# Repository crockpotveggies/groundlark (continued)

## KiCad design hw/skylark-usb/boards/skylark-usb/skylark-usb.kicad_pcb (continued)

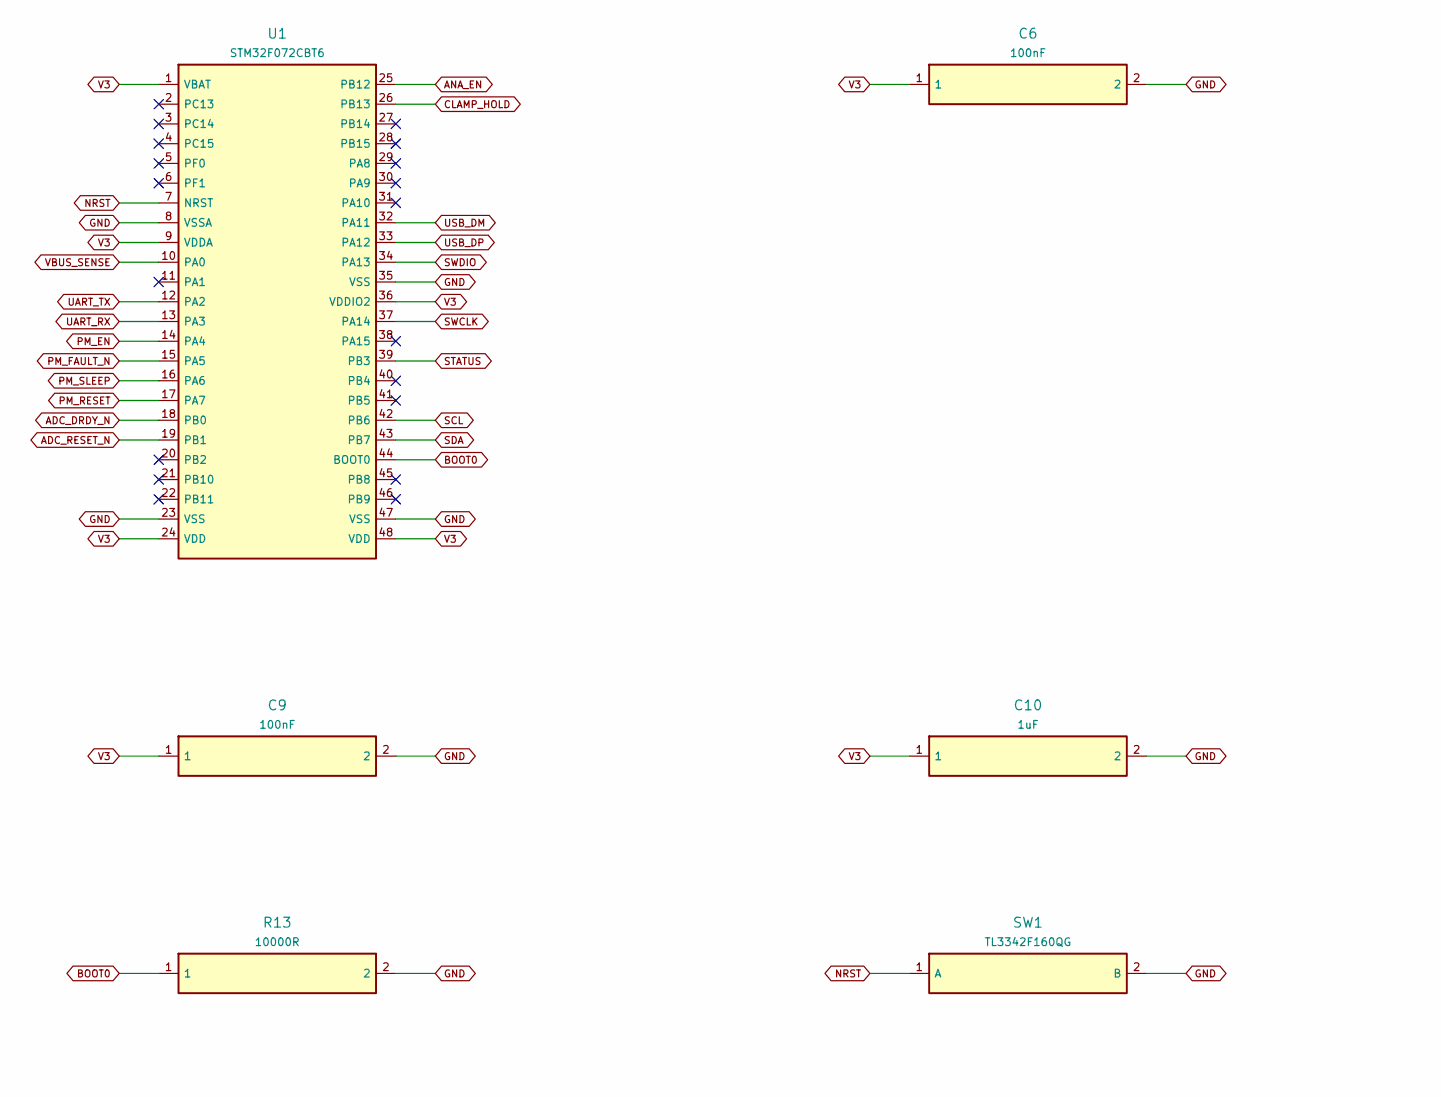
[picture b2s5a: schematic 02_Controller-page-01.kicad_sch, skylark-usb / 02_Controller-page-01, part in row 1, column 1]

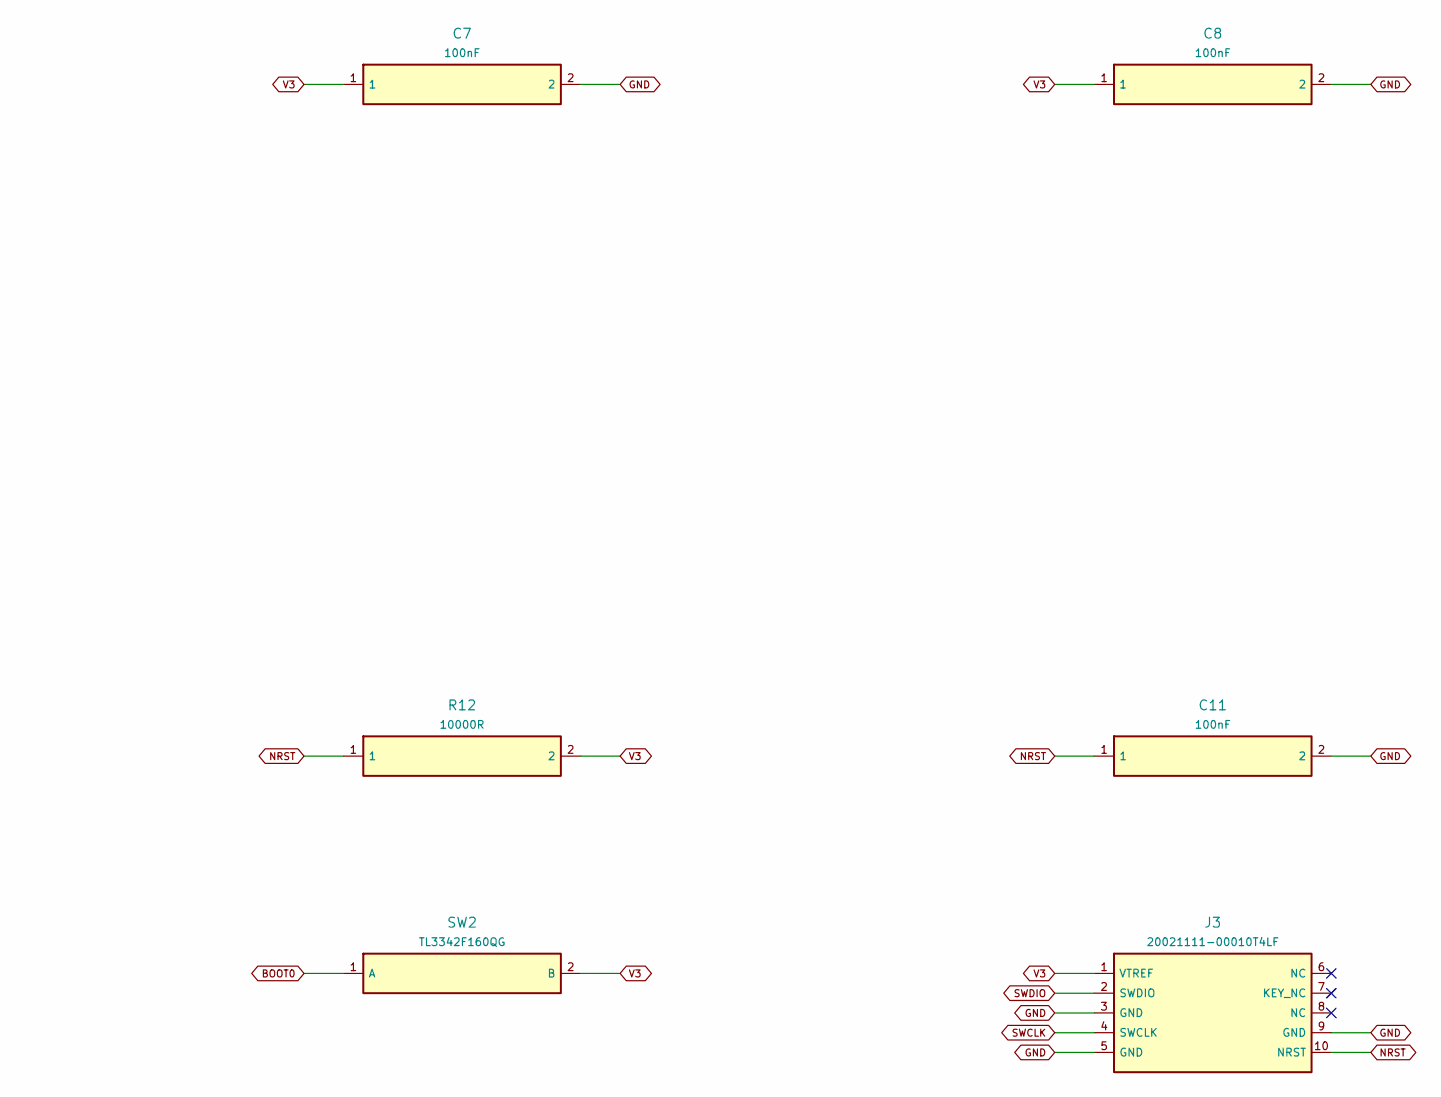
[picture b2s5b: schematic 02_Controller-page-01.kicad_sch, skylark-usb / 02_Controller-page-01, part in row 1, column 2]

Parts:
C6, C7, C8, C9, C11: 100nF; Capacitor_SMD__C_0603_1608Metric; MPN GRM188R71H104KA93D
C10: 1uF; Capacitor_SMD__C_0603_1608Metric; MPN GRM188R71E105KA12D
J3: 20021111-00010T4LF; Connector_PinHeader_1.27mm__PinHeader_2x05_P1.27mm_Vertical; MPN 20021111-00010T4LF
R12, R13: 10000R; Resistor_SMD__R_0603_1608Metric; MPN RT0603BRD0710KL
SW1, SW2: TL3342F160QG; Button_Switch_SMD__SW_SPST_TL3342; MPN TL3342F160QG
U1: STM32F072CBT6; Package_QFP__LQFP-48_7x7mm_P0.5mm; MPN STM32F072CBT6

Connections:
3: U1.3 (PC14)
4: U1.4 (PC15)
5: U1.5 (PF0)
6: J3.6 (NC)
11: U1.11 (PA1)
20: U1.20 (PB2)
21: U1.21 (PB10)
22: U1.22 (PB11)
27: U1.27 (PB14)
28: U1.28 (PB15)
29: U1.29 (PA8)
30: U1.30 (PA9)
31: U1.31 (PA10)
38: U1.38 (PA15)
40: U1.40 (PB4)
41: U1.41 (PB5)
45: U1.45 (PB8)
46: U1.46 (PB9)
ADC_DRDY_N: U1.18 (PB0); also elsewhere on the board
ADC_RESET_N: U1.19 (PB1); also elsewhere on the board
ANA_EN: U1.25 (PB12); also elsewhere on the board
BOOT0: R13.1, SW2.1 (A), U1.44 (BOOT0)
CLAMP_HOLD: U1.26 (PB13); also elsewhere on the board
GND: C6.2, C7.2, C8.2, C9.2, C10.2, C11.2, J3.3 (GND), J3.5 (GND), J3.9 (GND), R13.2, SW1.2 (B), U1.8 (VSSA), U1.23 (VSS), U1.35 (VSS), U1.47 (VSS); also elsewhere on the board
NRST: C11.1, J3.10 (NRST), R12.1, SW1.1 (A), U1.7 (NRST)
PM_EN: U1.14 (PA4); also elsewhere on the board
PM_FAULT_N: U1.15 (PA5); also elsewhere on the board
PM_RESET: U1.17 (PA7); also elsewhere on the board
PM_SLEEP: U1.16 (PA6); also elsewhere on the board
SCL: U1.42 (PB6); also elsewhere on the board
SDA: U1.43 (PB7); also elsewhere on the board
STATUS: U1.39 (PB3); also elsewhere on the board
SWCLK: J3.4 (SWCLK), U1.37 (PA14)
SWDIO: J3.2 (SWDIO), U1.34 (PA13)
UART_RX: U1.13 (PA3); also elsewhere on the board
UART_TX: U1.12 (PA2); also elsewhere on the board
USB_DM: U1.32 (PA11); also elsewhere on the board
USB_DP: U1.33 (PA12); also elsewhere on the board
V3: C6.1, C7.1, C8.1, C9.1, C10.1, J3.1 (VTREF), R12.2, SW2.2 (B), U1.1 (VBAT), U1.9 (VDDA), U1.24 (VDD), U1.36 (VDDIO2), U1.48 (VDD); also elsewhere on the board
VBUS_SENSE: U1.10 (PA0); also elsewhere on the board
j3-7: J3.7 (KEY_NC)
j3-8: J3.8 (NC)
u1-2: U1.2 (PC13)
u1-6: U1.6 (PF1)

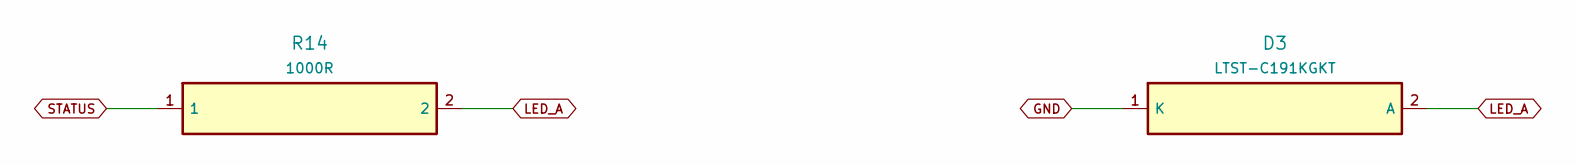
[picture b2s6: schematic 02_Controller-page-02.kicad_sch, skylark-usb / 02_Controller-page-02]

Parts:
D3: LTST-C191KGKT; LED_SMD__LED_0603_1608Metric; MPN LTST-C191KGKT
R14: 1000R; Resistor_SMD__R_0603_1608Metric; MPN RC0603FR-071KL

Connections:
GND: D3.1 (K); also elsewhere on the board
LED_A: D3.2 (A), R14.2
STATUS: R14.1; also elsewhere on the board

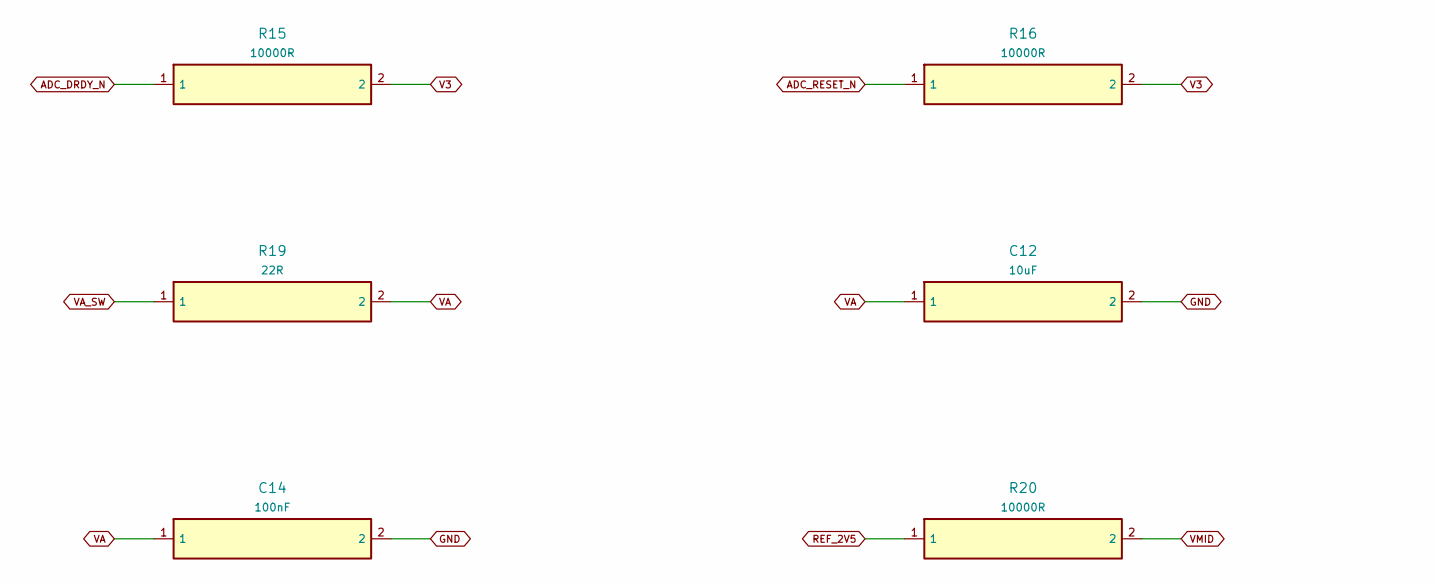
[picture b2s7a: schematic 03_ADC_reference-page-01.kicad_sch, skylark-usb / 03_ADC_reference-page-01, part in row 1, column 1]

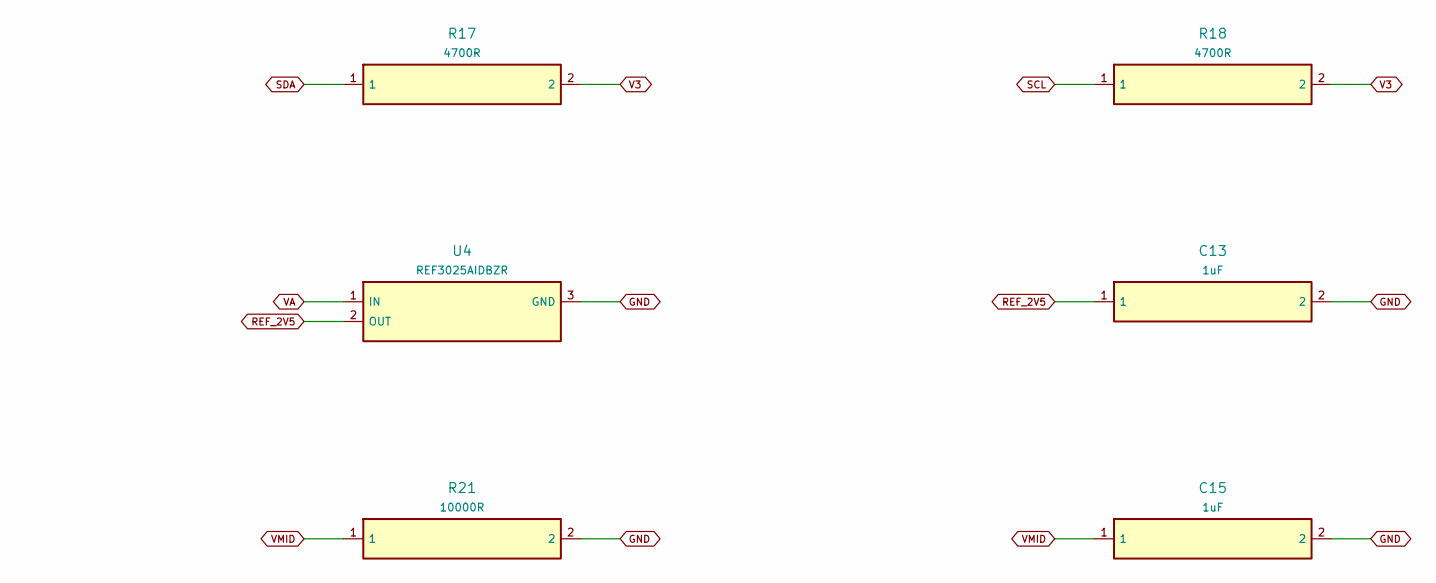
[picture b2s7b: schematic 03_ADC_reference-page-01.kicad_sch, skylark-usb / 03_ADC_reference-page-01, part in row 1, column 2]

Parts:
C12: 10uF; Capacitor_SMD__C_0805_2012Metric; MPN GRM21BR61A106KE19L
C13, C15: 1uF; Capacitor_SMD__C_0603_1608Metric; MPN GRM188R71E105KA12D
C14: 100nF; Capacitor_SMD__C_0603_1608Metric; MPN GRM188R71H104KA93D
R15, R16, R20, R21: 10000R; Resistor_SMD__R_0603_1608Metric; MPN RT0603BRD0710KL
R17, R18: 4700R; Resistor_SMD__R_0603_1608Metric; MPN RC0603FR-074K7L
R19: 22R; Resistor_SMD__R_0603_1608Metric; MPN RC0603FR-0722RL
U4: REF3025AIDBZR; Package_TO_SOT_SMD__SOT-23; MPN REF3025AIDBZR

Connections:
ADC_DRDY_N: R15.1; also elsewhere on the board
ADC_RESET_N: R16.1; also elsewhere on the board
GND: C12.2, C13.2, C14.2, C15.2, R21.2, U4.3 (GND); also elsewhere on the board
REF_2V5: C13.1, R20.1, U4.2 (OUT); also elsewhere on the board
SCL: R18.1; also elsewhere on the board
SDA: R17.1; also elsewhere on the board
V3: R15.2, R16.2, R17.2, R18.2; also elsewhere on the board
VA: C12.1, C14.1, R19.2, U4.1 (IN); also elsewhere on the board
VA_SW: R19.1; also elsewhere on the board
VMID: C15.1, R20.2, R21.1; also elsewhere on the board

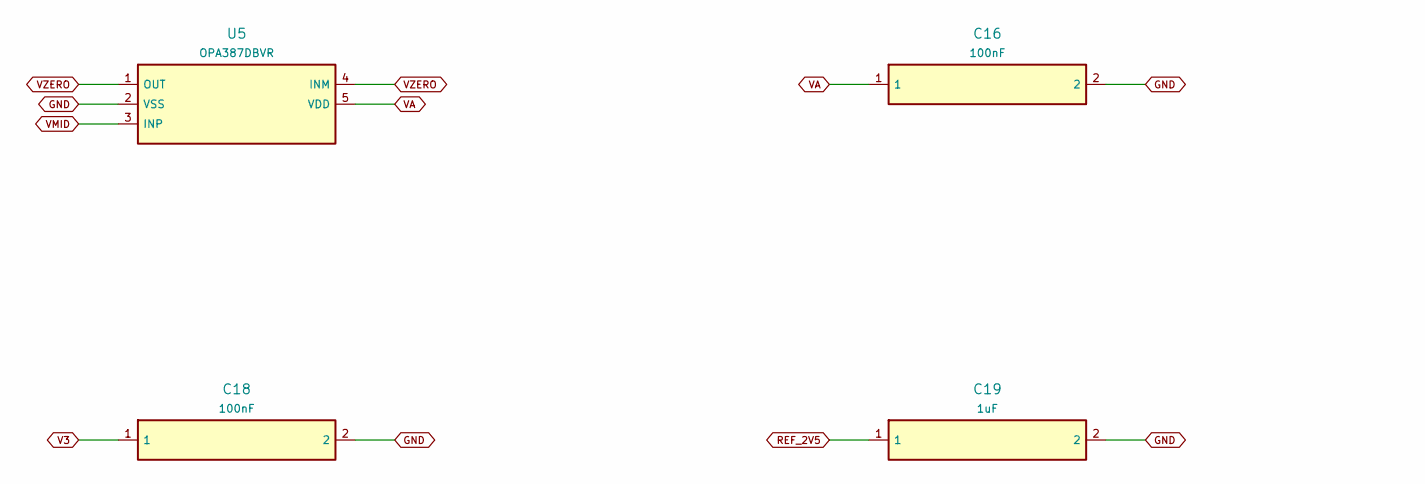
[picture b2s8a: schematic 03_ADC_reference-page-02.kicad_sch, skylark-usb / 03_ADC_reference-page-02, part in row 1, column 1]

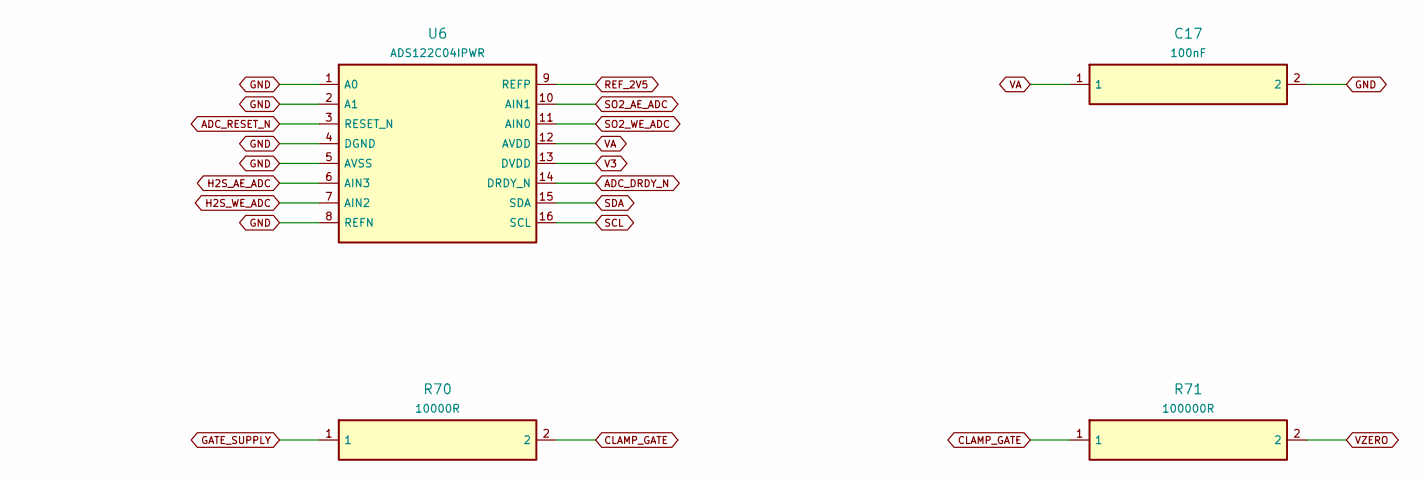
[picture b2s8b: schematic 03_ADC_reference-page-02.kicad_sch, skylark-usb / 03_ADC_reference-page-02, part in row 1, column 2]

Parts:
C16, C17, C18: 100nF; Capacitor_SMD__C_0603_1608Metric; MPN GRM188R71H104KA93D
C19: 1uF; Capacitor_SMD__C_0603_1608Metric; MPN GRM188R71E105KA12D
R70: 10000R; Resistor_SMD__R_0603_1608Metric; MPN RT0603BRD0710KL
R71: 100000R; Resistor_SMD__R_0603_1608Metric; MPN RT0603BRD07100KL
U5: OPA387DBVR; Package_TO_SOT_SMD__SOT-23-5; MPN OPA387DBVR
U6: ADS122C04IPWR; Package_SO__TSSOP-16_4.4x5mm_P0.65mm; MPN ADS122C04IPWR

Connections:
ADC_DRDY_N: U6.14 (DRDY_N); also elsewhere on the board
ADC_RESET_N: U6.3 (RESET_N); also elsewhere on the board
CLAMP_GATE: R70.2, R71.1; also elsewhere on the board
GATE_SUPPLY: R70.1; also elsewhere on the board
GND: C16.2, C17.2, C18.2, C19.2, U5.2 (VSS), U6.1 (A0), U6.2 (A1), U6.4 (DGND), U6.5 (AVSS), U6.8 (REFN); also elsewhere on the board
H2S_AE_ADC: U6.6 (AIN3); also elsewhere on the board
H2S_WE_ADC: U6.7 (AIN2); also elsewhere on the board
REF_2V5: C19.1, U6.9 (REFP); also elsewhere on the board
SCL: U6.16 (SCL); also elsewhere on the board
SDA: U6.15 (SDA); also elsewhere on the board
SO2_AE_ADC: U6.10 (AIN1); also elsewhere on the board
SO2_WE_ADC: U6.11 (AIN0); also elsewhere on the board
V3: C18.1, U6.13 (DVDD); also elsewhere on the board
VA: C16.1, C17.1, U5.5 (VDD), U6.12 (AVDD); also elsewhere on the board
VMID: U5.3 (INP); also elsewhere on the board
VZERO: R71.2, U5.1 (OUT), U5.4 (INM); also elsewhere on the board

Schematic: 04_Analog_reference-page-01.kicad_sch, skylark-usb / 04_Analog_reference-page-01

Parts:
C73: 1uF; Capacitor_SMD__C_0603_1608Metric; MPN GRM188R71E105KA12D
C74: 10nF; Capacitor_SMD__C_0603_1608Metric; MPN GRM188R71H103KA01D
D4: BAT54LT1G; Package_TO_SOT_SMD__SOT-23; MPN BAT54LT1G
Q7: MMBT3904LT1G; Package_TO_SOT_SMD__SOT-23; MPN MMBT3904LT1G
R72: 100000R; Resistor_SMD__R_0603_1608Metric; MPN RT0603BRD07100KL
R73, R74: 10000R; Resistor_SMD__R_0603_1608Metric; MPN RT0603BRD0710KL
U13: TPS22918DBVR; Package_TO_SOT_SMD__SOT-23-6; MPN TPS22918DBVR

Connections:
2: D4.2 (S)
ANA_CT: C74.1, U13.4 (CT)
ANA_EN: R72.1, U13.3 (ON); also elsewhere on the board
CLAMP_BASE: Q7.1 (G), R74.2
CLAMP_GATE: Q7.3 (D); also elsewhere on the board
CLAMP_HOLD: R73.2, R74.1; also elsewhere on the board
GATE_SUPPLY: D4.3 (D); also elsewhere on the board
GND: C73.2, C74.2, R72.2, U13.2 (GND); also elsewhere on the board
USB_5V: D4.1 (G); also elsewhere on the board
V3: C73.1, R73.1, U13.1 (VIN); also elsewhere on the board
VA_SW: U13.5 (QOD), U13.6 (VOUT); also elsewhere on the board
VZERO: Q7.2 (S); also elsewhere on the board

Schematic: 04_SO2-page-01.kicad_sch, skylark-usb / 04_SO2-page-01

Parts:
C30, C33: 100nF; Capacitor_SMD__C_1206_3216Metric; MPN C3216C0G1H104JT000N
C31: 10uF; Capacitor_SMD__C_0805_2012Metric; MPN GRM21BR61A106KE19L
GS1: SGX-7SO2-AQ-20; SGX7_AQ_Socket; MPN SGX-7SO2-AQ-20
Q1: MMBFJ270; Package_TO_SOT_SMD__SOT-23; MPN MMBFJ270
R30, R33: 20R; Resistor_SMD__R_0603_1608Metric; MPN RT0603BRD0720RL
R31, R34: 100000R; Resistor_SMD__R_0603_1608Metric; MPN RT0603BRD07100KL
R32: 10000R; Resistor_SMD__R_0603_1608Metric; MPN RT0603BRD0710KL
U7: OPA2387DGKR; Package_SO__VSSOP-8_3x3mm_P0.65mm; MPN OPA2387DGKR
U8: OPA387DBVR; Package_TO_SOT_SMD__SOT-23-5; MPN OPA387DBVR

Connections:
CLAMP_GATE: Q1.3 (G); also elsewhere on the board
GND: C31.2, U7.4 (VSS), U8.2 (VSS); also elsewhere on the board
SO2_AE: GS1.AE (Auxiliary), R33.1; also elsewhere on the board
SO2_AE_OUT: C33.2, R34.2, U7.7 (OUT_B); also elsewhere on the board
SO2_AE_SUM: C33.1, R33.2, R34.1, U7.6 (INM_B)
SO2_CE: GS1.CE (Counter); also elsewhere on the board
SO2_CE_DRV: U8.1 (OUT); also elsewhere on the board
SO2_RE: GS1.RE (Reference), Q1.2 (S); also elsewhere on the board
SO2_RE_FB: U8.4 (INM); also elsewhere on the board
SO2_WE: GS1.WE (Working), Q1.1 (D), R30.1
SO2_WE_ADC: C31.1, R32.2; also elsewhere on the board
SO2_WE_OUT: C30.2, R31.2, R32.1, U7.1 (OUT_A)
SO2_WE_SUM: C30.1, R30.2, R31.1, U7.2 (INM_A)
VA: U7.8 (VDD), U8.5 (VDD); also elsewhere on the board
VZERO: U7.3 (INP_A), U7.5 (INP_B), U8.3 (INP); also elsewhere on the board

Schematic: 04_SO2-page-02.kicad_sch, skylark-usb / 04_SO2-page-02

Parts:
C34: 10uF; Capacitor_SMD__C_0805_2012Metric; MPN GRM21BR61A106KE19L
C36: 100nF; Capacitor_SMD__C_1206_3216Metric; MPN C3216C0G1H104JT000N
C37, C38: 100nF; Capacitor_SMD__C_0603_1608Metric; MPN GRM188R71H104KA93D
Q2: MMBFJ270; Package_TO_SOT_SMD__SOT-23; MPN MMBFJ270
R35, R36: 10000R; Resistor_SMD__R_0603_1608Metric; MPN RT0603BRD0710KL
R37, R75: 100R; Resistor_SMD__R_0603_1608Metric; MPN RC0603FR-07100RL

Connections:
CLAMP_GATE: Q2.3 (G); also elsewhere on the board
GND: C34.2, C37.2, C38.2; also elsewhere on the board
GUARD: R75.2
SO2_AE: Q2.1 (D); also elsewhere on the board
SO2_AE_ADC: C34.1, R35.2; also elsewhere on the board
SO2_AE_OUT: R35.1; also elsewhere on the board
SO2_CE: R37.2; also elsewhere on the board
SO2_CE_DRV: C36.1, R37.1; also elsewhere on the board
SO2_RE: Q2.2 (S), R36.1; also elsewhere on the board
SO2_RE_FB: C36.2, R36.2; also elsewhere on the board
VA: C37.1, C38.1; also elsewhere on the board
VZERO: R75.1; also elsewhere on the board

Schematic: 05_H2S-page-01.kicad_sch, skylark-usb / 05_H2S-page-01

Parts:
C50, C53: 100nF; Capacitor_SMD__C_1206_3216Metric; MPN C3216C0G1H104JT000N
C51: 10uF; Capacitor_SMD__C_0805_2012Metric; MPN GRM21BR61A106KE19L
GS2: SGX-7H2S-AQ-25; SGX7_AQ_Socket; MPN SGX-7H2S-AQ-25
Q3: MMBFJ270; Package_TO_SOT_SMD__SOT-23; MPN MMBFJ270
R50, R53: 20R; Resistor_SMD__R_0603_1608Metric; MPN RT0603BRD0720RL
R51, R54: 20000R; Resistor_SMD__R_0603_1608Metric; MPN RT0603BRD0720KL
R52: 10000R; Resistor_SMD__R_0603_1608Metric; MPN RT0603BRD0710KL
U9: OPA2387DGKR; Package_SO__VSSOP-8_3x3mm_P0.65mm; MPN OPA2387DGKR
U10: OPA387DBVR; Package_TO_SOT_SMD__SOT-23-5; MPN OPA387DBVR

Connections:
CLAMP_GATE: Q3.3 (G); also elsewhere on the board
GND: C51.2, U9.4 (VSS), U10.2 (VSS); also elsewhere on the board
H2S_AE: GS2.AE (Auxiliary), R53.1; also elsewhere on the board
H2S_AE_OUT: C53.2, R54.2, U9.7 (OUT_B); also elsewhere on the board
H2S_AE_SUM: C53.1, R53.2, R54.1, U9.6 (INM_B); also elsewhere on the board
H2S_CE: GS2.CE (Counter); also elsewhere on the board
H2S_CE_DRV: U10.1 (OUT); also elsewhere on the board
H2S_RE: GS2.RE (Reference), Q3.2 (S); also elsewhere on the board
H2S_RE_FB: U10.4 (INM); also elsewhere on the board
H2S_WE: GS2.WE (Working), Q3.1 (D), R50.1
H2S_WE_ADC: C51.1, R52.2; also elsewhere on the board
H2S_WE_OUT: C50.2, R51.2, R52.1, U9.1 (OUT_A); also elsewhere on the board
H2S_WE_SUM: C50.1, R50.2, R51.1, U9.2 (INM_A); also elsewhere on the board
VA: U9.8 (VDD), U10.5 (VDD); also elsewhere on the board
VZERO: U9.3 (INP_A), U9.5 (INP_B), U10.3 (INP); also elsewhere on the board

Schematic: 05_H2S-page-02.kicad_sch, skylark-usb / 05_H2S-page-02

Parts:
C54: 10uF; Capacitor_SMD__C_0805_2012Metric; MPN GRM21BR61A106KE19L
C56, C80, C81, C82, C83: 100nF; Capacitor_SMD__C_1206_3216Metric; MPN C3216C0G1H104JT000N
C57, C58: 100nF; Capacitor_SMD__C_0603_1608Metric; MPN GRM188R71H104KA93D
Q4: MMBFJ270; Package_TO_SOT_SMD__SOT-23; MPN MMBFJ270
R55, R56: 10000R; Resistor_SMD__R_0603_1608Metric; MPN RT0603BRD0710KL
R57: 100R; Resistor_SMD__R_0603_1608Metric; MPN RC0603FR-07100RL

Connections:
CLAMP_GATE: Q4.3 (G); also elsewhere on the board
GND: C54.2, C57.2, C58.2; also elsewhere on the board
H2S_AE: Q4.1 (D); also elsewhere on the board
H2S_AE_ADC: C54.1, R55.2; also elsewhere on the board
H2S_AE_OUT: R55.1; also elsewhere on the board
H2S_CE: R57.2; also elsewhere on the board
H2S_CE_DRV: C56.1, R57.1; also elsewhere on the board
H2S_RE: Q4.2 (S), R56.1; also elsewhere on the board
H2S_RE_FB: C56.2, R56.2; also elsewhere on the board
H2S_WE_OUT: C80.2, C81.2, C82.2, C83.2; also elsewhere on the board
H2S_WE_SUM: C80.1, C81.1, C82.1, C83.1; also elsewhere on the board
VA: C57.1, C58.1; also elsewhere on the board

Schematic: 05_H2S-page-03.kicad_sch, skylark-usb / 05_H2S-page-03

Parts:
C84, C85, C86, C87: 100nF; Capacitor_SMD__C_1206_3216Metric; MPN C3216C0G1H104JT000N

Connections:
H2S_AE_OUT: C84.2, C85.2, C86.2, C87.2; also elsewhere on the board
H2S_AE_SUM: C84.1, C85.1, C86.1, C87.1; also elsewhere on the board

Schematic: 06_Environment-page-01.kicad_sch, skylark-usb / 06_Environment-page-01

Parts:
C70, C71, C72: 100nF; Capacitor_SMD__C_0603_1608Metric; MPN GRM188R71H104KA93D
U11: SHT40-AD1F-R2; SHT40; MPN SHT40-AD1F-R2
U12: BMP388; MPN BMP388

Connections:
GND: C70.2, C71.2, C72.2, U11.4 (VSS), U12.3 (GND), U12.5 (I2C_ADDR), U12.8 (GND), U12.9 (GND); also elsewhere on the board
SCL: U11.2 (SCL), U12.2 (SCL); also elsewhere on the board
SDA: U11.1 (SDA), U12.4 (SDA); also elsewhere on the board
V3: C70.1, C71.1, C72.1, U11.3 (VDD), U12.1 (VDDIO), U12.6 (CSB), U12.10 (VDD); also elsewhere on the board
u12-7: U12.7 (INT)

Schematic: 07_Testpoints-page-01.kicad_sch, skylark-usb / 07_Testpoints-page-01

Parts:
TP1, TP2, TP3, TP4, TP5, TP6, TP7: Test pad 1mm; TestPoint__TestPoint_Pad_D1.0mm; MPN Test pad 1mm

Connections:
GND: TP1.1; also elsewhere on the board
PM_5V: TP7.1; also elsewhere on the board
REF_2V5: TP5.1; also elsewhere on the board
USB_5V: TP2.1; also elsewhere on the board
V3: TP3.1; also elsewhere on the board
VA: TP4.1; also elsewhere on the board
VZERO: TP6.1; also elsewhere on the board

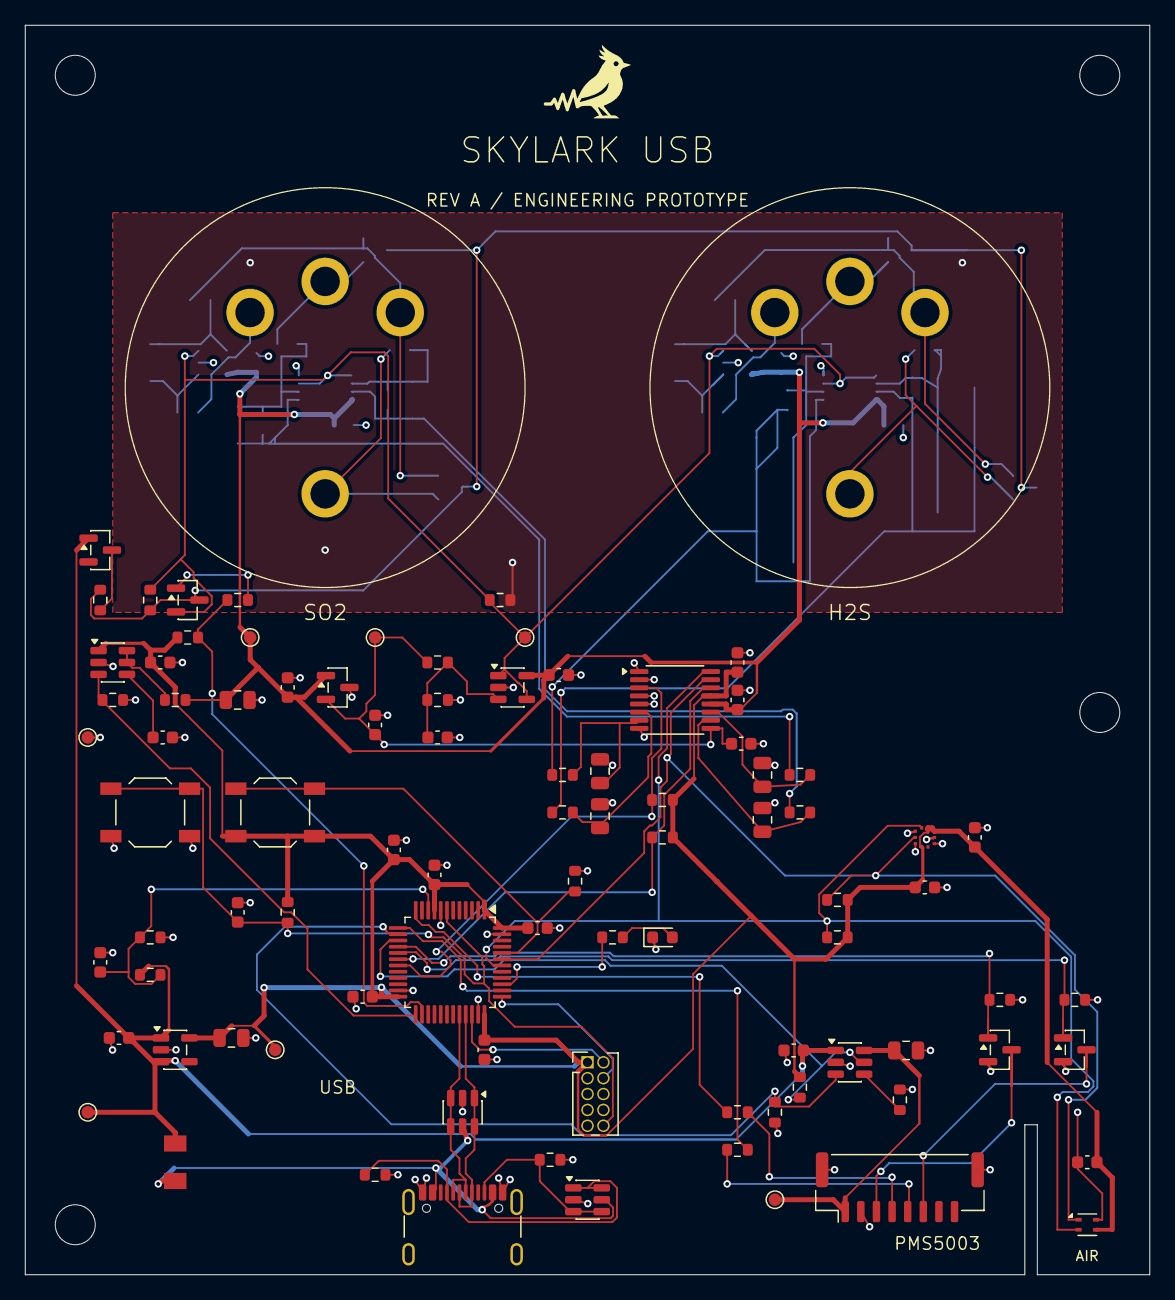
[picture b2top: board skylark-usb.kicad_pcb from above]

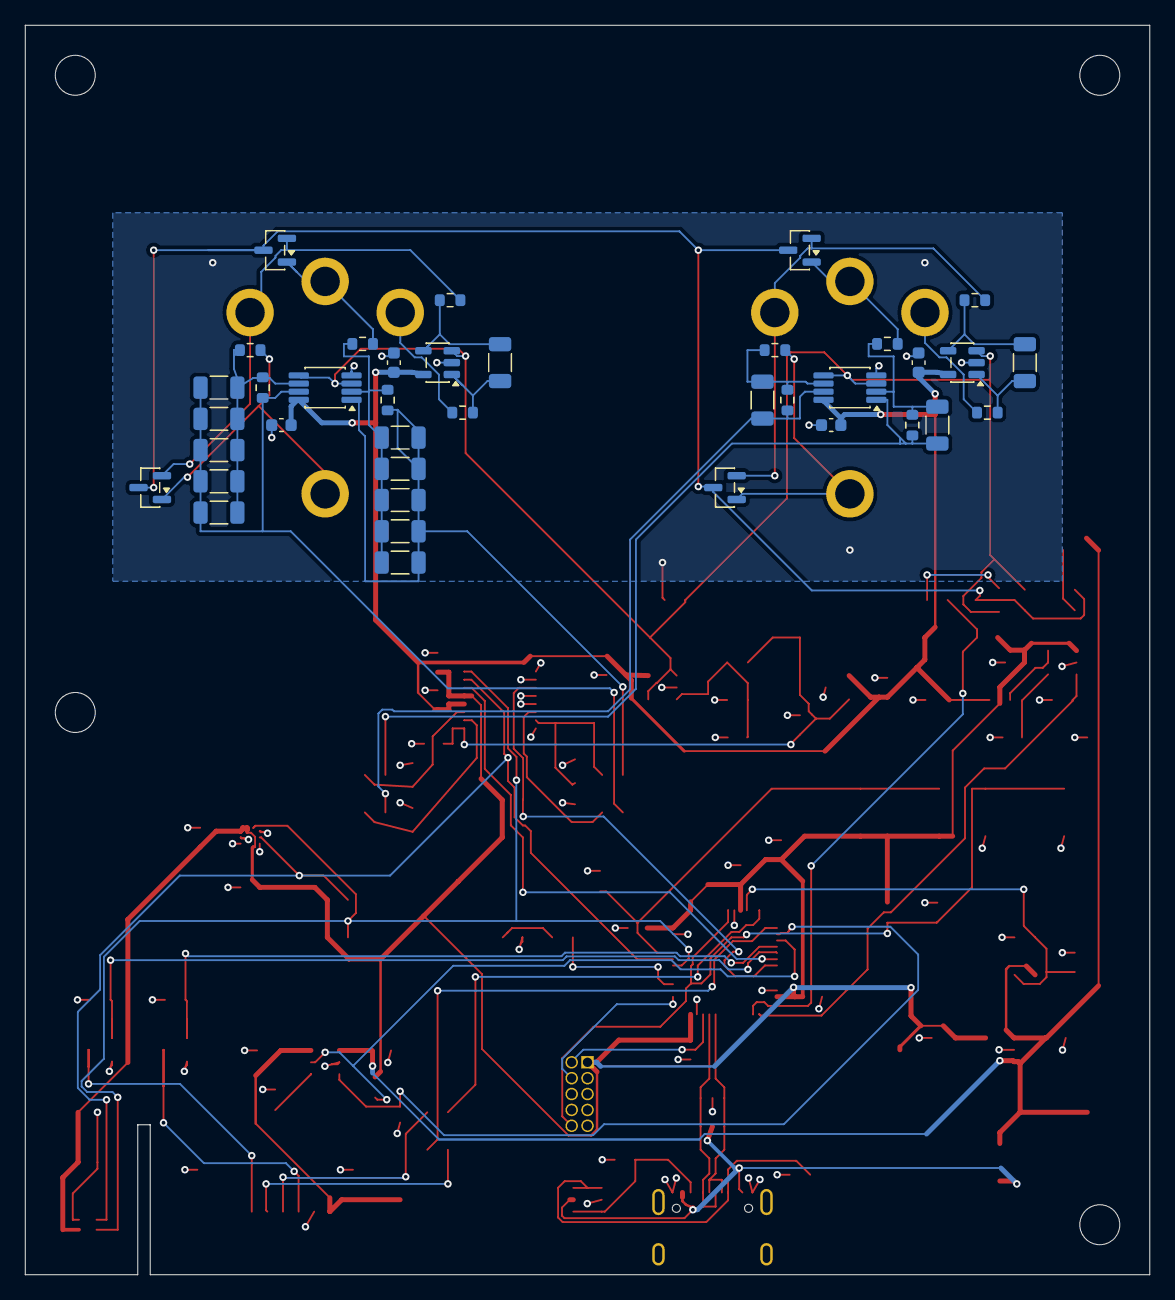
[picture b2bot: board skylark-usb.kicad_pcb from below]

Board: 4 copper layers, 90.0 x 100.0 mm, 132 parts (38 on the bottom side), 66 nets.

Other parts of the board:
H1, H2, H3, H4: M3; MountingHole__MountingHole_3.2mm_M3

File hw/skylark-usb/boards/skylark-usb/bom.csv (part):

Reference,Value,MPN,Footprint,DNP,Note
J1,TYPE-C-31-M-12,TYPE-C-31-M-12,USB_C_HRO_TYPE-C-31-M-12.kicad_mod,False,
R1,5100R,RC0603FR-075K1L,Resistor_SMD__R_0603_1608Metric.kicad_mod,False,
R2,5100R,RC0603FR-075K1L,Resistor_SMD__R_0603_1608Metric.kicad_mod,False,
D1,USBLC6-2SC6,USBLC6-2SC6,Package_TO_SOT_SMD__SOT-23-6.kicad_mod,False,
D2,USBLC6-2SC6,USBLC6-2SC6,Package_TO_SOT_SMD__SOT-23-6.kicad_mod,False,
F1,500mA PTC,1206L050YR,Fuse_1206.kicad_mod,False,
U2,AP2112K-3.3TRG1,AP2112K-3.3TRG1,Package_TO_SOT_SMD__SOT-23-5.kicad_mod,False,
C1,1uF,GRM188R71E105KA12D,Capacitor_SMD__C_0603_1608Metric.kicad_mod,False,
C2,4.7uF,GRM21BR71A475KA73L,Capacitor_SMD__C_0805_2012Metric.kicad_mod,False,
U3,TPS2553DBVR,TPS2553DBVR,Package_TO_SOT_SMD__SOT-23-6.kicad_mod,False,
R3,82000R,RC0603FR-0782KL,Resistor_SMD__R_0603_1608Metric.kicad_mod,False,
R4,100000R,RT0603BRD07100KL,Resistor_SMD__R_0603_1608Metric.kicad_mod,False,
R5,10000R,RT0603BRD0710KL,Resistor_SMD__R_0603_1608Metric.kicad_mod,False,
C3,100nF,GRM188R71H104KA93D,Capacitor_SMD__C_0603_1608Metric.kicad_mod,False,
C4,10uF,GRM21BR61A106KE19L,Capacitor_SMD__C_0805_2012Metric.kicad_mod,False,
J2,BM08B-GHS-TBT,BM08B-GHS-TBT,Connector_JST__JST_GH_BM08B-GHS-TBT_1x08-1MP_P1.25mm_Vertical.kicad_mod,False,Numbered 1:1 PMS5003 cable; verify both mating ends. PMS module separately enclosure-mounted.
Q5,2N7002/HAMR,2N7002/HAMR,Package_TO_SOT_SMD__SOT-23.kicad_mod,False,
Q6,2N7002/HAMR,2N7002/HAMR,Package_TO_SOT_SMD__SOT-23.kicad_mod,False,
R6,100000R,RT0603BRD07100KL,Resistor_SMD__R_0603_1608Metric.kicad_mod,False,
R7,100000R,RT0603BRD07100KL,Resistor_SMD__R_0603_1608Metric.kicad_mod,False,
R8,4700R,RC0603FR-074K7L,Resistor_SMD__R_0603_1608Metric.kicad_mod,False,
R9,4700R,RC0603FR-074K7L,Resistor_SMD__R_0603_1608Metric.kicad_mod,False,
R10,100000R,RT0603BRD07100KL,Resistor_SMD__R_0603_1608Metric.kicad_mod,False,
R11,100000R,RT0603BRD07100KL,Resistor_SMD__R_0603_1608Metric.kicad_mod,False,
C5,100nF,GRM188R71H104KA93D,Capacitor_SMD__C_0603_1608Metric.kicad_mod,False,
U1,STM32F072CBT6,STM32F072CBT6,Package_QFP__LQFP-48_7x7mm_P0.5mm.kicad_mod,False,
C6,100nF,GRM188R71H104KA93D,Capacitor_SMD__C_0603_1608Metric.kicad_mod,False,
C7,100nF,GRM188R71H104KA93D,Capacitor_SMD__C_0603_1608Metric.kicad_mod,False,
C8,100nF,GRM188R71H104KA93D,Capacitor_SMD__C_0603_1608Metric.kicad_mod,False,
C9,100nF,GRM188R71H104KA93D,Capacitor_SMD__C_0603_1608Metric.kicad_mod,False,
C10,1uF,GRM188R71E105KA12D,Capacitor_SMD__C_0603_1608Metric.kicad_mod,False,
R12,10000R,RT0603BRD0710KL,Resistor_SMD__R_0603_1608Metric.kicad_mod,False,
C11,100nF,GRM188R71H104KA93D,Capacitor_SMD__C_0603_1608Metric.kicad_mod,False,
R13,10000R,RT0603BRD0710KL,Resistor_SMD__R_0603_1608Metric.kicad_mod,False,
SW1,TL3342F160QG,TL3342F160QG,Button_Switch_SMD__SW_SPST_TL3342.kicad_mod,False,
SW2,TL3342F160QG,TL3342F160QG,Button_Switch_SMD__SW_SPST_TL3342.kicad_mod,False,
J3,20021111-00010T4LF,20021111-00010T4LF,Connector_PinHeader_1.27mm__PinHeader_2x05_P1.27mm_Vertical.kicad_mod,False,
R14,1000R,RC0603FR-071KL,Resistor_SMD__R_0603_1608Metric.kicad_mod,False,
D3,LTST-C191KGKT,LTST-C191KGKT,LED_SMD__LED_0603_1608Metric.kicad_mod,False,
R15,10000R,RT0603BRD0710KL,Resistor_SMD__R_0603_1608Metric.kicad_mod,False,
R16,10000R,RT0603BRD0710KL,Resistor_SMD__R_0603_1608Metric.kicad_mod,False,
R17,4700R,RC0603FR-074K7L,Resistor_SMD__R_0603_1608Metric.kicad_mod,False,
R18,4700R,RC0603FR-074K7L,Resistor_SMD__R_0603_1608Metric.kicad_mod,False,
R19,22R,RC0603FR-0722RL,Resistor_SMD__R_0603_1608Metric.kicad_mod,False,
C12,10uF,GRM21BR61A106KE19L,Capacitor_SMD__C_0805_2012Metric.kicad_mod,False,
U4,REF3025AIDBZR,REF3025AIDBZR,Package_TO_SOT_SMD__SOT-23.kicad_mod,False,
C13,1uF,GRM188R71E105KA12D,Capacitor_SMD__C_0603_1608Metric.kicad_mod,False,
C14,100nF,GRM188R71H104KA93D,Capacitor_SMD__C_0603_1608Metric.kicad_mod,False,
R20,10000R,RT0603BRD0710KL,Resistor_SMD__R_0603_1608Metric.kicad_mod,False,
R21,10000R,RT0603BRD0710KL,Resistor_SMD__R_0603_1608Metric.kicad_mod,False,
C15,1uF,GRM188R71E105KA12D,Capacitor_SMD__C_0603_1608Metric.kicad_mod,False,
U5,OPA387DBVR,OPA387DBVR,Package_TO_SOT_SMD__SOT-23-5.kicad_mod,False,
C16,100nF,GRM188R71H104KA93D,Capacitor_SMD__C_0603_1608Metric.kicad_mod,False,
U6,ADS122C04IPWR,ADS122C04IPWR,Package_SO__TSSOP-16_4.4x5mm_P0.65mm.kicad_mod,False,
C17,100nF,GRM188R71H104KA93D,Capacitor_SMD__C_0603_1608Metric.kicad_mod,False,
C18,100nF,GRM188R71H104KA93D,Capacitor_SMD__C_0603_1608Metric.kicad_mod,False,
C19,1uF,GRM188R71E105KA12D,Capacitor_SMD__C_0603_1608Metric.kicad_mod,False,
GS1,SGX-7SO2-AQ-20,SGX-7SO2-AQ-20,SGX7_AQ_Socket.kicad_mod,False,Four 0322-0-15-15-34-27-10-0 sockets; top footprint mirrors manufacturer bottom view; no direct cell soldering.
U7,OPA2387DGKR,OPA2387DGKR,Package_SO__VSSOP-8_3x3mm_P0.65mm.kicad_mod,False,
U8,OPA387DBVR,OPA387DBVR,Package_TO_SOT_SMD__SOT-23-5.kicad_mod,False,
R30,20R,RT0603BRD0720RL,Resistor_SMD__R_0603_1608Metric.kicad_mod,False,
R31,100000R,RT0603BRD07100KL,Resistor_SMD__R_0603_1608Metric.kicad_mod,False,
C30,100nF,C3216C0G1H104JT000N,Capacitor_SMD__C_1206_3216Metric.kicad_mod,False,C0G feedback/compensation; H2S feedback totals 500 nF in parallel
R32,10000R,RT0603BRD0710KL,Resistor_SMD__R_0603_1608Metric.kicad_mod,False,
C31,10uF,GRM21BR61A106KE19L,Capacitor_SMD__C_0805_2012Metric.kicad_mod,False,
Q1,MMBFJ270,MMBFJ270,Package_TO_SOT_SMD__SOT-23.kicad_mod,False,
R33,20R,RT0603BRD0720RL,Resistor_SMD__R_0603_1608Metric.kicad_mod,False,
R34,100000R,RT0603BRD07100KL,Resistor_SMD__R_0603_1608Metric.kicad_mod,False,
C33,100nF,C3216C0G1H104JT000N,Capacitor_SMD__C_1206_3216Metric.kicad_mod,False,C0G feedback/compensation; H2S feedback totals 500 nF in parallel
R35,10000R,RT0603BRD0710KL,Resistor_SMD__R_0603_1608Metric.kicad_mod,False,
C34,10uF,GRM21BR61A106KE19L,Capacitor_SMD__C_0805_2012Metric.kicad_mod,False,
Q2,MMBFJ270,MMBFJ270,Package_TO_SOT_SMD__SOT-23.kicad_mod,False,
R36,10000R,RT0603BRD0710KL,Resistor_SMD__R_0603_1608Metric.kicad_mod,False,
R37,100R,RC0603FR-07100RL,Resistor_SMD__R_0603_1608Metric.kicad_mod,False,
C36,100nF,C3216C0G1H104JT000N,Capacitor_SMD__C_1206_3216Metric.kicad_mod,False,C0G feedback/compensation; H2S feedback totals 500 nF in parallel
C37,100nF,GRM188R71H104KA93D,Capacitor_SMD__C_0603_1608Metric.kicad_mod,False,
C38,100nF,GRM188R71H104KA93D,Capacitor_SMD__C_0603_1608Metric.kicad_mod,False,
GS2,SGX-7H2S-AQ-25,SGX-7H2S-AQ-25,SGX7_AQ_Socket.kicad_mod,False,Four 0322-0-15-15-34-27-10-0 sockets; top footprint mirrors manufacturer bottom view; no direct cell soldering.
U9,OPA2387DGKR,OPA2387DGKR,Package_SO__VSSOP-8_3x3mm_P0.65mm.kicad_mod,False,
U10,OPA387DBVR,OPA387DBVR,Package_TO_SOT_SMD__SOT-23-5.kicad_mod,False,
R50,20R,RT0603BRD0720RL,Resistor_SMD__R_0603_1608Metric.kicad_mod,False,
R51,20000R,RT0603BRD0720KL,Resistor_SMD__R_0603_1608Metric.kicad_mod,False,
C50,100nF,C3216C0G1H104JT000N,Capacitor_SMD__C_1206_3216Metric.kicad_mod,False,C0G feedback/compensation; H2S feedback totals 500 nF in parallel
R52,10000R,RT0603BRD0710KL,Resistor_SMD__R_0603_1608Metric.kicad_mod,False,
C51,10uF,GRM21BR61A106KE19L,Capacitor_SMD__C_0805_2012Metric.kicad_mod,False,
Q3,MMBFJ270,MMBFJ270,Package_TO_SOT_SMD__SOT-23.kicad_mod,False,
R53,20R,RT0603BRD0720RL,Resistor_SMD__R_0603_1608Metric.kicad_mod,False,
R54,20000R,RT0603BRD0720KL,Resistor_SMD__R_0603_1608Metric.kicad_mod,False,
C53,100nF,C3216C0G1H104JT000N,Capacitor_SMD__C_1206_3216Metric.kicad_mod,False,C0G feedback/compensation; H2S feedback totals 500 nF in parallel
R55,10000R,RT0603BRD0710KL,Resistor_SMD__R_0603_1608Metric.kicad_mod,False,
C54,10uF,GRM21BR61A106KE19L,Capacitor_SMD__C_0805_2012Metric.kicad_mod,False,
Q4,MMBFJ270,MMBFJ270,Package_TO_SOT_SMD__SOT-23.kicad_mod,False,
R56,10000R,RT0603BRD0710KL,Resistor_SMD__R_0603_1608Metric.kicad_mod,False,
R57,100R,RC0603FR-07100RL,Resistor_SMD__R_0603_1608Metric.kicad_mod,False,
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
